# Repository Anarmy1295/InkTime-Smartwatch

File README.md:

# InkTime-Smartwatch

An open-source smartwatch powered by the nRF52840 with an e-paper display, designed for low power consumption and BLE connectivity.

## Block Diagram

## BOM (Bill Of Materials) 
| Qty | Component | Value / Part | Package | Notes |
|-----|----------|-------------|--------|------|
| 3 | Buttons | EVP-AKE31A | SMD | SW_DN, SW_ENT, SW_UP |
| 1 | Solder Jumper | SJ1 | SMD | Configuration jumper |
| 3 | Resistor | 7.68kΩ | 0201 | R2, R3, R4 |
| 4 | Capacitor | 0.1µF | 0201 | Decoupling |
| 1 | Capacitor | 0.1µF / 50V | 0402 | EPD |
| 1 | Resistor | 0Ω / 0.47Ω | 0201 | EPD driver |
| 1 | Capacitor | 1µF | 0402 | General |
| 5 | Capacitor | 100nF | 0402 | Decoupling |
| 1 | Capacitor | 100pF | 0402 | Filtering |
| 6 | Resistor | 10kΩ | 0201 | Pull-ups / general |
| 1 | Capacitor | 10µF | 0201 | Bulk |
| 2 | Capacitor | 10µF | 0402 | Power |
| 1 | Inductor | 10µH | 0402 | DC/DC |
| 4 | Capacitor | 12pF | 0402 | Crystal load |
| 1 | Inductor | 15nH | 0402 | RF matching |
| 2 | Capacitor | 1pF | 0402 | RF |
| 6 | Capacitor | 1µF | 0201 | Decoupling |
| 9 | Capacitor | 1µF / 50V | 0402 | EPD |
| 1 | Resistor | 2.2kΩ | 0201 | Config |
| 1 | PMOS | DMG2305UX | SOT-23 | Power switching |
| 2 | Capacitor | 22µF | 0402 | Power rail |
| 1 | Antenna | 2450AT18B100E | 1206 | 2.4GHz |
| 1 | Inductor | 3.9nH | 0402 | RF matching |
| 1 | Crystal | 32.768kHz | 3215 | RTC |
| 1 | Crystal | 32MHz | 2016 | MCU clock |
| 2 | Resistor | 3.3kΩ | 0201 | General |
| 1 | Capacitor | 4.7µF | 0402 | Bulk |
| 5 | Capacitor | 4.7µF | 0402 | Decoupling |
| 1 | Capacitor | 47nF | 0402 | Filtering |
| 1 | FPC Connector | 503480-2400 | SMD | Display |
| 2 | Resistor | 5.1kΩ | 0201 | USB-C CC |
| 1 | Inductor | 68µH | SMD | Power |
| 1 | Capacitor | 820pF | 0402 | Filtering |
| 1 | Accelerometer | BMA421 | LGA | Sensor |
| 1 | Charger IC | BQ25180YBGR | BGA | LiPo charger |
| 1 | Haptic Driver | DRV2605YZFR | BGA | Motor driver |
| 1 | Inductor | 0.47µH | 2012 | Power stage |
| 14 | Test Points | TP pads | PCB | Debug |
| 1 | USB-C | KH-TYPE-C-16P | SMD | Power |
| 1 | Fuel Gauge | MAX17048G+T10 | TDFN-8 | Battery monitor |
| 3 | Diode | MBR0530 | SOD-123 | Schottky |
| 3 | Capacitor | N.C. | 0402 | Not populated |
| 1 | MCU | nRF52840 | QFN | Main MCU |
| 1 | Buck-Boost | RT6160AWSC | WLCSP | 3.3V rail |
| 1 | NMOS | SI1308EDL | SOT-323 | Switching |
| 1 | Debug Connector | TC2030-IDC | PCB | SWD |
| 1 | ESD Protection | USBLC6-2SC6Y | SOT-23-6 | USB protection |

## Hardware Description

### MCU — nRF52840

The nRF52840 is the central processing unit of the system.

**Key features:**
- ARM Cortex-M4F @ 64 MHz (with FPU)
- Bluetooth Low Energy (BLE 5.0)
- USB 2.0 Full Speed
- 1 MB Flash / 256 KB RAM

All peripherals are connected via:
- I2C
- SPI
- GPIO

---

### Power Architecture

USB-C → BQ25180 (charger) → LiPo battery (AKY0106, 400 mAh)
→ 3.3V rail (VREG, for MCU and all peripherals)

Battery → RT6160AWSC (boost) → EPD high-voltage supply (VCOM, gate voltages)

#### BQ25180 (Charger IC)

- Charges the LiPo battery
- Provides system rail (VSYS)
- I2C communication with MCU
- Interrupt output for status/fault

#### RT6160 (Buck-Boost Regulator)

- Converts VSYS to stable 3.3V
- Powers:
  - MCU
  - sensors
  - display
  - haptic driver

#### MAX17048 (Fuel Gauge)

- Monitors battery voltage and state of charge
- I2C interface
- ALERT signal for battery events

---

### E-Paper Display

Controlled via SPI and GPIO.

#### Interface

| Signal | Direction | Description |
|--------|----------|------------|
| SCK | MCU → Display | SPI clock |
| MOSI | MCU → Display | SPI data |
| EPD_CS | MCU → Display | Chip select |
| EPD_DC | MCU → Display | Data/Command |
| EPD_RST | MCU → Display | Reset |
| EPD_BUSY | Display → MCU | Status |

#### Power Stage

Includes:
- inductors
- Schottky diodes
- MOSFETs

Generates:
- PREVGH
- PREVGL

---

### IMU — BMA421

- Interface: I2C
- Features:
  - acceleration sensing
  - motion detection
  - step counting

**Interrupts:**
- INT1
- INT2

---

### Haptic Driver — DRV2605

- Interface: I2C
- Enable pin: `HAPTIC_EN`
- Function: vibration motor control

---

### USB Interface

- USB Type-C connector
- ESD protection: USBLC6-2SC6Y

**Signals:**
- VBUS
- D+
- D-

**Usage:**
- charging
- USB detection

---

### RF & Antenna

- 2.4 GHz chip antenna (2450AT18B100E)

**Design includes:**
- matching network
- antenna keepout
- no copper under antenna

---

### User Interface

3 buttons:
- Up
- Down
- Enter / Esc

- Connected to GPIO
- Active-low

---

### Debug Interface

SWD via Tag-Connect:

- SWDIO
- SWDCLK
- RESET
- SWO
- 3.3V
- GND

---

## Pin Mapping (nRF52840)

### I2C (Shared Bus)

| Pin | Function |
|-----|---------|
| P0.06 | SDA |
| P0.07 | SCL |

Devices:
- BMA421
- MAX17048
- BQ25180
- RT6160
- DRV2605

---

### SPI (E-Paper Display)

| Pin | Function |
|-----|---------|
| P0.02 | SCK |
| P0.03 | MOSI |
| P0.05 | CS |
| P0.15 | DC |
| P0.16 | RST |
| P0.17 | BUSY |

---

### Control & Interrupts

| Pin | Function |
|-----|---------|
| P1.01 | Display power (PFET) |
| P0.08 | BMA421 INT1 |
| P1.08 | BMA421 INT2 |
| P0.10 | MAX17048 ALERT |
| P0.11 | Charger interrupt |
| P0.12 | Haptic enable |

---

### Buttons

| Pin | Function |
|-----|---------|
| P0.13 | Up |
| P0.14 | Down |
| P1.00 | Enter / Esc |

---

### USB

| Signal | Function |
|--------|---------|
| D+ | Data |
| D- | Data |
| VBUS | Power detect |

---

### Clocks & Debug

- SWDIO / SWDCLK / RESET / SWO
- 32 MHz crystal (HFXO)
- 32.768 kHz crystal (LFXO)

---

## Design Considerations

- Use of dedicated hardware interfaces (I2C, SPI)
- Logical grouping of signals
- Simplified PCB routing
- Interrupt-driven architecture
- Clean debug interface

---

## Power Optimization

- MCU supports low-power modes
- E-paper consumes power only during refresh
- IMU is ultra low-power
- Haptic driver active only briefly

**Efficiency strategies:**
- enable peripherals only when needed
- regulated 3.3V rail
- independent control of display power

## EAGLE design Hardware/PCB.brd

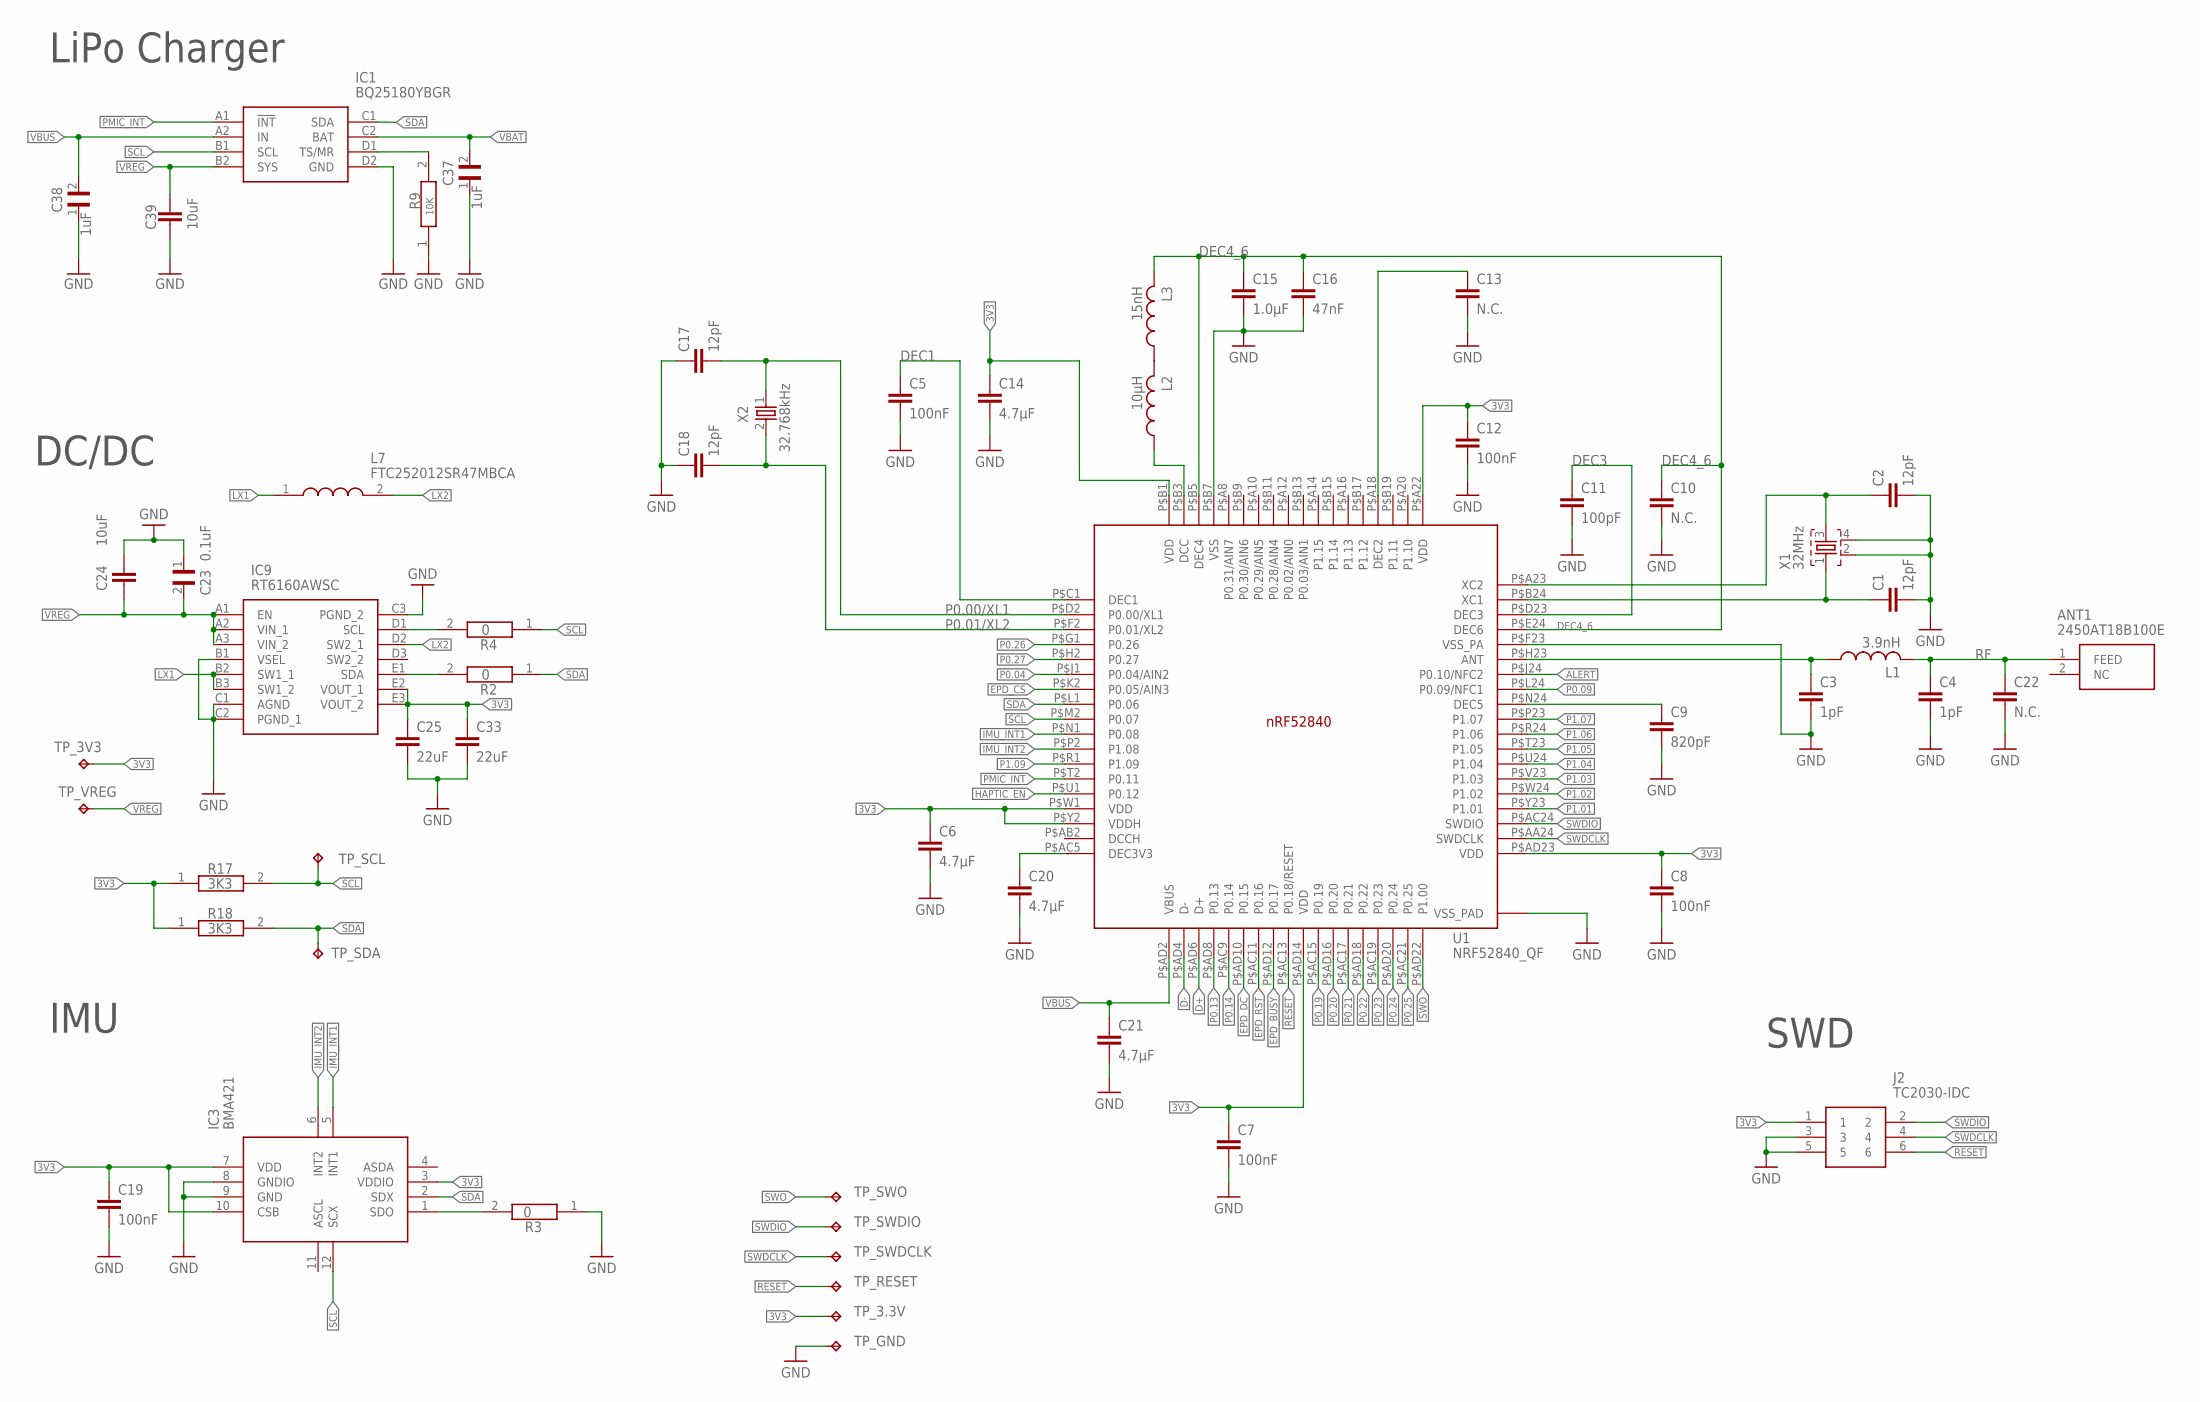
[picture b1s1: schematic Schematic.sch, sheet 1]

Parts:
ANT1: 2450AT18B100E; 2450AT18B100E_ANTC3216X140N
C1, C2, C17, C18: 12pF; PERFECT_0402_0402
C3, C4: 1pF; PERFECT_0402_0402
C5, C7, C8, C12, C19: 100nF; PERFECT_0402_0402
C6, C14, C20, C21: 4.7μF; PERFECT_0402_0402
C9: 820pF; PERFECT_0402_0402
C10, C13, C22: N.C.; PERFECT_0402_0402
C11: 100pF; PERFECT_0402_0402
C15: 1.0μF; PERFECT_0402_0402
C16: 47nF; PERFECT_0402_0402
C23: 0.1uF; GRM011R60J152KE01L_1_0201
C24: 10uF; PERFECT_0402_0402
C25, C33: 22uF; PERFECT_0402_0402
C37, C38: 1uF; GRM011R60J152KE01L_1_0201
C39: 10uF; NORDIC_NRF_3_RESC0402_N
IC1: BQ25180YBGR; BQ25180YBGR_BGA8C40P2X4_100X155X50
IC3: BMA421; BMA423_BMA423
IC9: RT6160AWSC; RT6160AWSC_BGA15C40P3X5_140X230X60
J2: TC2030-IDC; TC2030-IDC_TC2030IDC
L1: 3.9nH; NORDIC_NRF_2_RESC0402_L
L2: 10μH; NORDIC_NRF_2_RESC0402_L
L3: 15nH; NORDIC_NRF_2_RESC0402_L
L7: FTC252012SR47MBCA; MLP2016SR47MT0S1_INDC2016X100N
R2, R3, R4: 0; CPF0201D7K68C1_0201
R9: 10K; CPF0201D7K68C1_0201
R17, R18: 3K3; CPF0201D7K68C1_0201
TP_3.3V, TP_3V3: HECTOR_WATCH_1_TPTP20R; HECTOR_WATCH_1_TP20R
TP_GND: HECTOR_WATCH_1_TPTP20R; HECTOR_WATCH_1_TP20R
TP_RESET: HECTOR_WATCH_1_TPTP20R; HECTOR_WATCH_1_TP20R
TP_SCL: HECTOR_WATCH_1_TPTP20R; HECTOR_WATCH_1_TP20R
TP_SDA: HECTOR_WATCH_1_TPTP20R; HECTOR_WATCH_1_TP20R
TP_SWDCLK: HECTOR_WATCH_1_TPTP20R; HECTOR_WATCH_1_TP20R
TP_SWDIO: HECTOR_WATCH_1_TPTP20R; HECTOR_WATCH_1_TP20R
TP_SWO: HECTOR_WATCH_1_TPTP20R; HECTOR_WATCH_1_TP20R
TP_VREG: HECTOR_WATCH_1_TPTP20R; HECTOR_WATCH_1_TP20R
U1: NRF52840_QF; NORDIC_NRF_4_AQFN50P700X700X85_HS-74N
X1: 32MHz; NORDIC_NRF_BT-XTAL_2016_N
X2: 32.768kHz; NORDIC_NRF_1_XTAL_3215_N

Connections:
3V3: C6.1, C7.1, C8.1, C12.1, C14.1, C19.1, C25.1, C33.1, IC3.3 (VDDIO), IC3.7 (VDD), IC3.10 (CSB), IC9.E2 (VOUT_1), IC9.E3 (VOUT_2), J2.1, R17.1, R18.1, TP_3.3V.TP, TP_3V3.TP, U1.P$A22 (VDD), U1.P$AD14 (VDD), U1.P$AD23 (VDD), U1.P$B1 (VDD), U1.P$W1 (VDD), U1.P$Y2 (VDDH); also elsewhere on the board
ALERT: U1.P$J24 (P0.10/NFC2); also elsewhere on the board
D+: U1.P$AD6 (D+); also elsewhere on the board
D-: U1.P$AD4 (D-); also elsewhere on the board
DEC1: C5.1, U1.P$C1 (DEC1)
DEC3: C11.1, U1.P$D23 (DEC3)
DEC4_6: C10.1, C15.1, C16.1, L3.2, U1.P$B5 (DEC4), U1.P$E24 (DEC6)
EPD_BUSY: U1.P$AD12 (P0.17); also elsewhere on the board
EPD_CS: U1.P$K2 (P0.05/AIN3); also elsewhere on the board
EPD_DC: U1.P$AD10 (P0.15); also elsewhere on the board
EPD_RST: U1.P$AC11 (P0.16); also elsewhere on the board
GND: C1.2, C2.2, C3.2, C4.2, C5.2, C6.2, C7.2, C8.2, C9.2, C10.2, C11.2, C12.2, C13.2, C14.2, C15.2, C16.2, C17.1, C18.1, C19.2, C20.2, C21.2, C22.2, C23.1, C24.1, C25.2, C33.2, C37.1, C38.1, C39.2, IC1.D2 (GND), IC3.8 (GNDIO), IC3.9 (GND), IC9.B1 (VSEL), IC9.C1 (AGND), IC9.C2 (PGND_1), IC9.C3 (PGND_2), J2.3, J2.5, R3.1, R9.1, TP_GND.TP, U1.P$74 (VSS_PAD), U1.P$75 (VSS_PAD), U1.P$76 (VSS_PAD), U1.P$77 (VSS_PAD), U1.P$78 (VSS_PAD), U1.P$79 (VSS_PAD), U1.P$80 (VSS_PAD), U1.P$81 (VSS_PAD), U1.P$82 (VSS_PAD), U1.P$83 (VSS_PAD), U1.P$84 (VSS_PAD), U1.P$85 (VSS_PAD), U1.P$86 (VSS_PAD), U1.P$87 (VSS_PAD), U1.P$88 (VSS_PAD), U1.P$89 (VSS_PAD), U1.P$90 (VSS_PAD), U1.P$B7 (VSS), U1.P$F23 (VSS_PA), X1.2, X1.4; also elsewhere on the board
HAPTIC_EN: U1.P$U1 (P0.12); also elsewhere on the board
IMU_INT1: IC3.5 (INT1), U1.P$N1 (P0.08)
IMU_INT2: IC3.6 (INT2), U1.P$P2 (P1.08)
LX1: IC9.B2 (SW1_1), IC9.B3 (SW1_2), L7.1
LX2: IC9.D2 (SW2_1), L7.2
unnamed: IC9.D1 (SCL), R4.2
unnamed: IC9.E1 (SDA), R2.2
unnamed: IC1.D1 (TS/MR), R9.2
unnamed: C9.1, U1.P$N24 (DEC5)
unnamed: L2.2, L3.1
unnamed: C3.1, L1.1, U1.P$H23 (ANT)
unnamed: IC3.1 (SDO), R3.2
unnamed: L2.1, U1.P$B3 (DCC)
unnamed: C1.1, U1.P$B24 (XC1), X1.1
unnamed: C2.1, U1.P$A23 (XC2), X1.3
unnamed: C20.1, U1.P$AC5 (DEC3V3)
unnamed: C13.1, U1.P$A18 (DEC2)
P0.00/XL1: C17.2, U1.P$D2 (P0.00/XL1), X2.1
P0.01/XL2: C18.2, U1.P$F2 (P0.01/XL2), X2.2
P0.04: U1.P$J1 (P0.04/AIN2)
P0.09: U1.P$L24 (P0.09/NFC1)
P0.13: U1.P$AD8 (P0.13); also elsewhere on the board
P0.14: U1.P$AC9 (P0.14); also elsewhere on the board
P0.19: U1.P$AC15 (P0.19)
P0.20: U1.P$AD16 (P0.20)
P0.21: U1.P$AC17 (P0.21)
P0.22: U1.P$AD18 (P0.22)
P0.23: U1.P$AC19 (P0.23)
P0.24: U1.P$AD20 (P0.24)
P0.25: U1.P$AC21 (P0.25)
P0.26: U1.P$G1 (P0.26)
P0.27: U1.P$H2 (P0.27)
P1.01: U1.P$Y23 (P1.01); also elsewhere on the board
P1.02: U1.P$W24 (P1.02); also elsewhere on the board
P1.03: U1.P$V23 (P1.03)
P1.04: U1.P$U24 (P1.04)
P1.05: U1.P$T23 (P1.05)
P1.06: U1.P$R24 (P1.06)
P1.07: U1.P$P23 (P1.07)
P1.09: U1.P$R1 (P1.09)
PMIC_INT: IC1.A1 (!INT), U1.P$T2 (P0.11)
RESET: J2.6, TP_RESET.TP, U1.P$AC13 (P0.18/RESET)
RF: ANT1.1 (FEED), C4.1, C22.1, L1.2
SCL: IC1.B1 (SCL), IC3.12 (SCX), R4.1, R17.2, TP_SCL.TP, U1.P$M2 (P0.07); also elsewhere on the board
SDA: IC1.C1 (SDA), IC3.2 (SDX), R2.1, R18.2, TP_SDA.TP, U1.P$L1 (P0.06); also elsewhere on the board
SWDCLK: J2.4, TP_SWDCLK.TP, U1.P$AA24 (SWDCLK)
SWDIO: J2.2, TP_SWDIO.TP, U1.P$AC24 (SWDIO)
SWO: TP_SWO.TP, U1.P$AD22 (P1.00)
VBAT: C37.2, IC1.C2 (BAT); also elsewhere on the board
VBUS: C21.1, C38.2, IC1.A2 (IN), U1.P$AD2 (VBUS); also elsewhere on the board
VREG: C23.2, C24.2, C39.1, IC1.B2 (SYS), IC9.A1 (EN), IC9.A2 (VIN_1), IC9.A3 (VIN_2), TP_VREG.TP

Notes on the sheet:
LiPo Charger
DC/DC
IMU
SWD

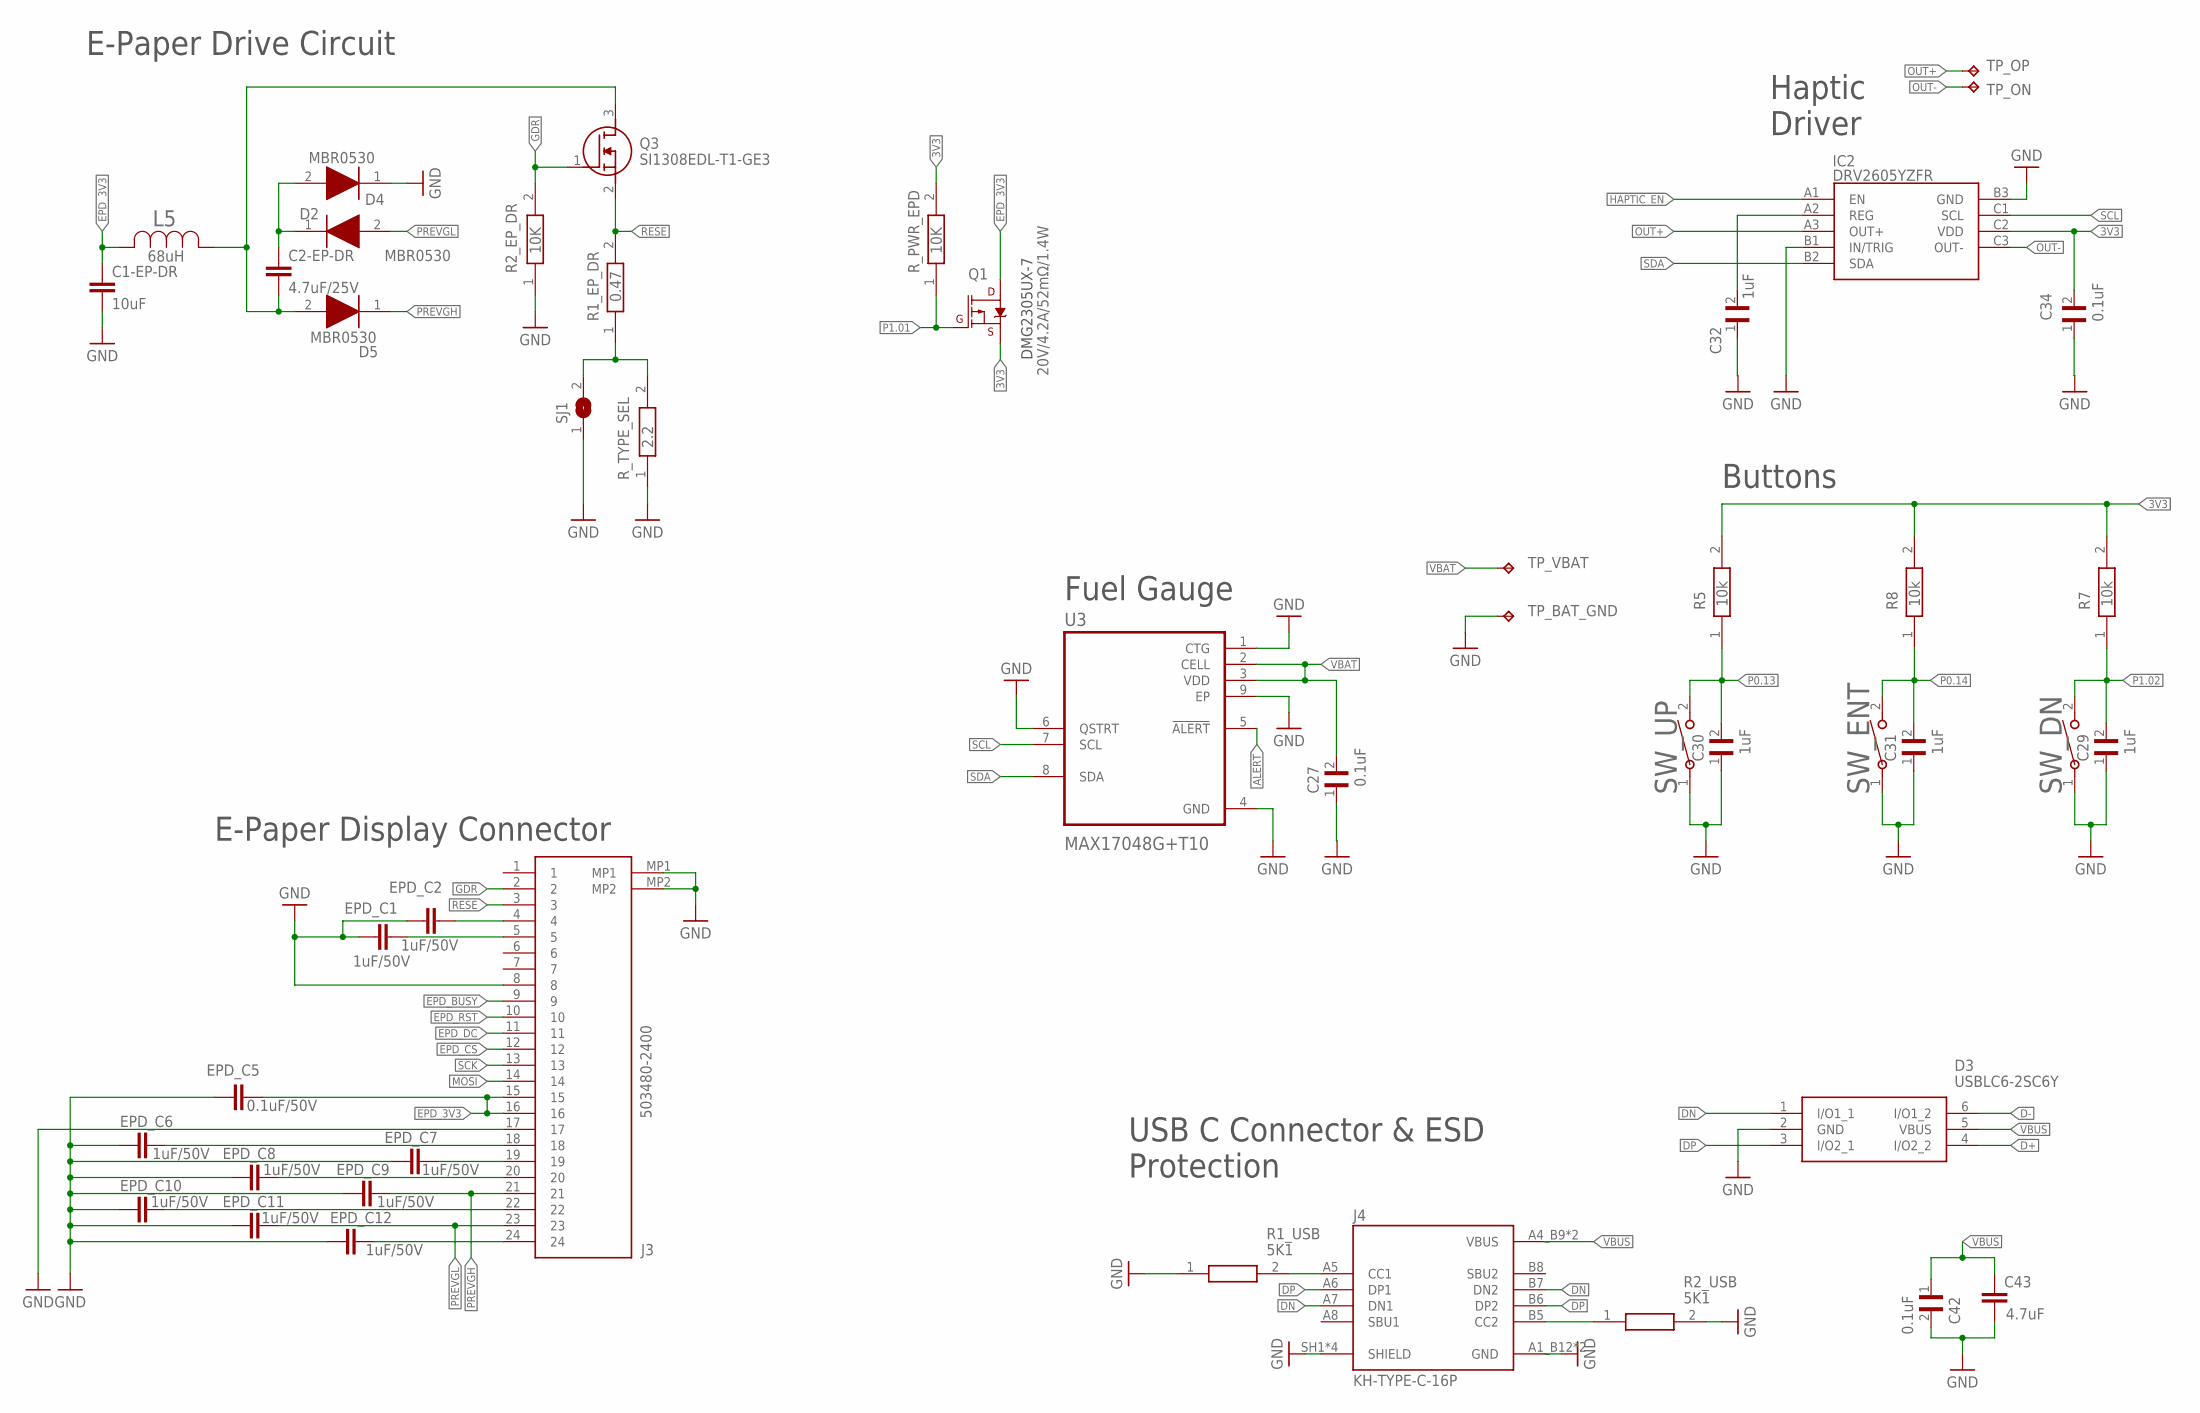
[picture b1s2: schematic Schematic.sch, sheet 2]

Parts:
C1-EP-DR: 10uF; PERFECT_0402_0402
C2-EP-DR: 4.7uF/25V; PERFECT_0402_0402
C27, C34, C42: 0.1uF; GRM011R60J152KE01L_1_0201
C29, C30, C31, C32: 1uF; GRM011R60J152KE01L_1_0201
C43: 4.7uF; PERFECT_0402_0402
D2, D4, D5: MBR0530; ESP32_C6_LIBRARY_5_SOD3716X135N
D3: USBLC6-2SC6Y; ESP32_C6_LIBRARY_3_SOT95P280X145-6N
EPD_C1, EPD_C2, EPD_C6, EPD_C7, EPD_C8, EPD_C9, EPD_C10, EPD_C11, EPD_C12: 1uF/50V; PERFECT_0402_0402
EPD_C5: 0.1uF/50V; PERFECT_0402_0402
IC2: DRV2605YZFR; DRV2605YZFR_BGA9C50P3X3_144X144X62
J3: 503480-2400; 503480-2400_5034802400
J4: KH-TYPE-C-16P; KH-TYPE-C-16P_KINGHELM_KH-TYPE-C-16P
L5: 68uH; ESP32_C6_LIBRARY_2_IND_4828-WE-TPC_WRE
Q1: 20V/4.2A/52mΩ/1.4W; ESP32_C6_LIBRARY_4_ESP32_C6_LIBRARY_4_ESP32_C6_LIBRARY_4_ES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
Q3: SI1308EDL-T1-GE3; ESP32_C6_LIBRARY_6_SOT65P210X110-3N
R1_EP_DR: 0.47; CPF0201D7K68C1_0201
R1_USB, R2_USB: 5K1; CPF0201D7K68C1_0201
R2_EP_DR: 10K; CPF0201D7K68C1_0201
R5, R7, R8: 10k; CPF0201D7K68C1_0201
R_PWR_EPD: 10K; CPF0201D7K68C1_0201
R_TYPE_SEL: 2.2; CPF0201D7K68C1_0201
SJ1: ESP32_C6_LIBRARY_7_JUMPER_SJ
SW_DN: 2025-10-22_07-23-44_LIBRARY_EVP-AKE31ASW_EVP-AKE3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; 2025-10-22_07-23-44_LIBRARY_SW_EVP-AKE31A_PAN
SW_ENT: 2025-10-22_07-23-44_LIBRARY_EVP-AKE31ASW_EVP-AKE3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; 2025-10-22_07-23-44_LIBRARY_SW_EVP-AKE31A_PAN
SW_UP: 2025-10-22_07-23-44_LIBRARY_EVP-AKE31ASW_EVP-AKE3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; 2025-10-22_07-23-44_LIBRARY_SW_EVP-AKE31A_PAN
TP_BAT_GND: HECTOR_WATCH_1_TPTP20R; HECTOR_WATCH_1_TP20R
TP_ON: HECTOR_WATCH_1_TPTP20R; HECTOR_WATCH_1_TP20R
TP_OP: HECTOR_WATCH_1_TPTP20R; HECTOR_WATCH_1_TP20R
TP_VBAT: HECTOR_WATCH_1_TPTP20R; HECTOR_WATCH_1_TP20R
U3: MAX17048G+T10; ESP32_C6_LIBRARY_SON50P200X200X80-9N

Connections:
3V3: C34.2, IC2.C2 (VDD), Q1.2 (S), R5.2, R7.2, R8.2, R_PWR_EPD.2; also elsewhere on the board
ALERT: U3.5 (!ALERT); also elsewhere on the board
D+: D3.4 (I/O2_2); also elsewhere on the board
D-: D3.6 (I/O1_2); also elsewhere on the board
DN: D3.1 (I/O1_1), J4.A7 (DN1), J4.B7 (DN2)
DP: D3.3 (I/O2_1), J4.A6 (DP1), J4.B6 (DP2)
EPD_3V3: C1-EP-DR.1, EPD_C5.2, J3.15, J3.16, L5.2, Q1.3 (D)
EPD_BUSY: J3.9; also elsewhere on the board
EPD_CS: J3.12; also elsewhere on the board
EPD_DC: J3.11; also elsewhere on the board
EPD_RST: J3.10; also elsewhere on the board
GDR: J3.2, Q3.1 (G), R2_EP_DR.2
GND: C1-EP-DR.2, C27.1, C29.1, C30.1, C31.1, C32.1, C34.1, C42.2, C43.1, D3.2 (GND), D4.1 (K), EPD_C1.1, EPD_C2.1, EPD_C5.1, EPD_C6.1, EPD_C7.1, EPD_C8.1, EPD_C9.1, EPD_C10.1, EPD_C11.1, EPD_C12.1, IC2.B1 (IN/TRIG), IC2.B3 (GND), J3.8, J3.17, J3.MP1, J3.MP2, J4.A1_B12 (GND), J4.A12_B1 (GND), J4.SH1 (SHIELD), J4.SH2 (SHIELD), J4.SH3 (SHIELD), J4.SH4 (SHIELD), R1_USB.1, R2_EP_DR.1, R2_USB.2, R_TYPE_SEL.1, SJ1.1, SW_DN.1, SW_ENT.1, SW_UP.1, TP_BAT_GND.TP, U3.1 (CTG), U3.4 (GND), U3.6 (QSTRT), U3.9 (EP); also elsewhere on the board
HAPTIC_EN: IC2.A1 (EN); also elsewhere on the board
MOSI: J3.14
unnamed: J4.B5 (CC2), R2_USB.1
unnamed: J4.A5 (CC1), R1_USB.2
unnamed: C2-EP-DR.2, D5.2 (A), L5.1, Q3.3 (D)
unnamed: C2-EP-DR.1, D2.1 (K), D4.2 (A)
unnamed: R1_EP_DR.1, R_TYPE_SEL.2, SJ1.2
unnamed: EPD_C1.2, J3.5
unnamed: EPD_C2.2, J3.4
unnamed: EPD_C6.2, J3.18
unnamed: EPD_C7.2, J3.19
unnamed: EPD_C8.2, J3.20
unnamed: EPD_C10.2, J3.22
unnamed: EPD_C12.2, J3.24
unnamed: C32.2, IC2.A2 (REG)
OUT+: IC2.A3 (OUT+), TP_OP.TP
OUT-: IC2.C3 (OUT-), TP_ON.TP
P0.13: C30.2, R5.1, SW_UP.2; also elsewhere on the board
P0.14: C31.2, R8.1, SW_ENT.2; also elsewhere on the board
P1.01: Q1.1 (G), R_PWR_EPD.1; also elsewhere on the board
P1.02: C29.2, R7.1, SW_DN.2; also elsewhere on the board
PREVGH: D5.1 (K), EPD_C9.2, J3.21
PREVGL: D2.2 (A), EPD_C11.2, J3.23
RESE: J3.3, Q3.2 (S), R1_EP_DR.2
SCK: J3.13
SCL: IC2.C1 (SCL), U3.7 (SCL); also elsewhere on the board
SDA: IC2.B2 (SDA), U3.8 (SDA); also elsewhere on the board
VBAT: C27.2, TP_VBAT.TP, U3.2 (CELL), U3.3 (VDD); also elsewhere on the board
VBUS: C42.1, C43.2, D3.5 (VBUS), J4.A4_B9 (VBUS), J4.A9_B4 (VBUS); also elsewhere on the board

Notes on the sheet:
E-Paper Drive Circuit
DMG2305UX-7
E-Paper Display Connector
Fuel Gauge
Haptic Driver
Buttons
USB C Connector & ESD Protection

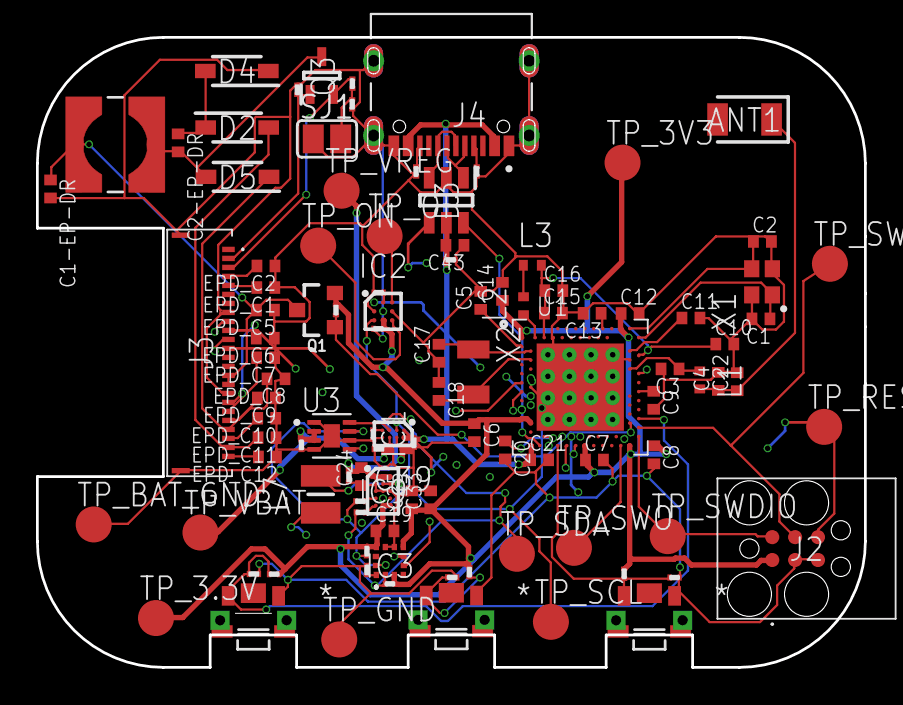
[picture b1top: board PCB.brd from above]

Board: 4 copper layers, 46.0 x 35.0 mm, 105 parts (0 on the bottom side), 68 nets.

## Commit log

2026-04-10 Initial project upload
2026-04-21 Added exploded view file

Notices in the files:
parts and their libraries:
COPYRIGHT: Copyright (C) 2024 Ultra Librarian. All rights reserved.
COPYRIGHT: Copyright (C) 2025 Ultra Librarian. All rights reserved.
